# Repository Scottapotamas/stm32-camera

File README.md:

# stm32-camera

Existing products are either cameras which lack resolution and image quality (640x480 security cams that happen to have UART outputs), or are higher end expensive options geared towards computer vision for embedded hardware (openMV, PixyCam, etc).

This project seeks to provide higher quality still photos or short low-fps videos in an integrated device, allowing for greater integration flexibility whilst minimising power consumption.

# Project Goals

- Sample a CMOS camera sensor using a microcontroller. Condition the data as appropriate, and hold images in memory.
- Allow upload of image data to the host over a serial, USB, or other connection.
- Aim to minimise current draw wherever possible, and design around the ability to 'deep-sleep' for maximum power savings.
- Support a wide range of lenses for different application requirements.
- Allow the host to control functionality such as exposure, capture modes, resolution, and power saving functionality.
- Cost less than $65
- Provide source for interfacing a host device like an Arduino/STM32.
- Provide software sources for the camera board to allow modified behaviour.

# Bonus Features

- Control either an onboard or off-board LED flash. Use a DAC output to drive it for variable brightness.
- Control a IR filter switch mechanism to add or subtract IR filtering automatically at night.
- Include hardware light sensing to detect ambient light without use of the camera (for IR filter switch, dynamic flash brightness, etc).
- Ability to store images or image sequences on disk, and/or copy them off later when the action dies down.

# Approach

- Small 32x32mm PCB with camera sensor, lens mount (uses 20mm spaced M2 screws), microcontroller.
- STM32F4 microcontroller interfaces to the sensor and provides power management, filter swaps, storage etc.
- The IO pinout is 2.54mm 8-way through hole. Accepts 4-14V DC input power. Has UART, and 3 high feature set expansion IO.
- Mounting hole pattern is somewhat backwards compatible with 28mm spaced M3 holes.

# Hardware Overview

- Its a 4 layer board due to the density of the fanout and smaller board package. 
- Min track width/clearance is 0.22mm and min via is 0.35mm. No blind or buried vias.
- While a bit tight, it should be fine with better 'budget' Chinese fabs. OSHPark would have absolutely no issues with it.
- Specific notes are in [the electronics folder](Electronics)

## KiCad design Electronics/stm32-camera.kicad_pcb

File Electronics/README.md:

# Electronics Notes

General implementation notes during assignment and schematic capture. These are notes which don't make it onto the schematic due to length or relevance. Hopefully they might be useful during software dev.

# Microcontroller Pin Assignment

- I2C2 peripheral is used for SSCB interface (configuration registers).
- MCO (PA8) is used for the camera XCLK clock. Should clock at 24Mhz typical, 6Mhz minimum. This can be the HSI, HSE, a timer, etc.
- DCMI interface is used for main camera connection (includes HSYNC/VSYNC/PIXCK pins etc)
- PCLK is the camera strobe for 8-bit data on rising edge.
- PWDN is the camera power down signal (active high). Connected to PE3.
- RES is camera reset signal (active low). Connected to PE2
- SDIO interface is used in 4-bit mode for SD card. In theory, we should be able to write images to the SD card at highish speed, then allow the host to pull them off later if needed.
- SWD with SWO is enabled explicitly. Plan on using CORTEX 10-pin header.
- HSE clock included. Probably use a 16MHz CERALOCK instead of usual 8MHz?
- DAC2 is proposed for use with a flash driver. Ideally don't use PWM as switching noise is potentially visible, but that same pin can also be an analog input, PWM output or general GPIO.

# Sensor Specifics

## Power Down Options

| Hardware Control  | Software Control |
| ----------------- | ---------------- |
| PWDN is pulled high to stop the clock  | i2c commands available but doesn't stop everything (clocks) |
| Power draw is apparently 15uA.  | Registers are retained but draws 1mA.  |

Later on in the datasheet, this is conflicted by:

> For OV2640, there have big power down current, so power down mode is not supported by OV2640 for power saving.

The lower voltage LDO's have their EN line connected to the micro for more granular/forceful control.
I'll likely just use hardware control as long as it configures fast enough.

## Reset

A full hardware reset is performed when RESETB goes low.

There is also reset via the i2c interface.

## Other lines

- The datasheet states that strobe mode allows it to operate with an external flash and(/or?) LED. 
- The pinmap guide states this defaults as an input, but is the flash control output.
- A STM32 GPIO is connected instead of flash driver (at least to know if the camera wants a flash, probably redundant info by the time we see it)

# SD Card

# IR Cut Filter Switcher

As far as I can tell, its a bistable solenoid which moves the IR cut filter infront or away from the sensor.

## Theory

The [aliexpress page I got my samples from](https://www.aliexpress.com/item/HD-3MP-IR-CUT-filter-M12-lens-Metal-mount-double-filter-switcher-for-cctv-camera-IRCUT/32785570950.html?spm=2114.13010608.0.0.Kv2NdH ) has no real information other than images (but hey, $2.50AUD).

This [ebay page](http://www.ebay.com/itm/400938137287) seems to have more info (copied below)

- Working Voltage: 5V-18V
- Rated Current: 0.2A
- Screw thread interface: M12 Mount (MTV / C)
- Switcher Type: Pendulum Switcher
- Filter: Phosphate Filter
- Glass Size: 11*9.3mm
- Hole Spacing: 20mm
- Total length: 30mm. Inner Diameter: 15mm

I found another page with similar looking units which states the following:

- Start voltage: 1.8V±10%
- Applied voltage: 3.0V±10%
- Driver pulse width: 50ms
- Trigger current: 100mA or less
- Working current: 200mA or less

~~If the filter needs to be held in place during aquisition then some interesting software might need to manage the power consumption cleverly.~~ Pendulum switching means a short pulse high or low to set and forget. Drive with inverted polarity to change back.
This seems to vary between modules. Some of the other samples I received later *are* spring loaded.

It appears the units I recieved use a 1.25mm pitch molex(?) 2-pin connector. 
I'm pretty sure its molex because locking tab instead of slot. 
Seems like a Picoblade connector.

## Testing

Tests with bench supply show switching latches setting after power is removed.

With the supply set to 3.000V, the minimum current which triggers a full switch is 60mA. At 40mA and above, it appears to half-hold and reset on removal of power. Below 40mA nothing happens.

Switching would not occur at 2.0V. At 2.5V 50mA was able to activate the shutter, but 60-70mA was more reliable.

At 3.250V (rough design target for regulator and hence micro VDD) 45mA was enough to trigger a switch but sounded 'slower'. It seems the solenoid will draw 54mA, or 0.175W.

As some of these cameras will be in potentially extreme outdoor environments, a switching unit was cooled to -10°C and tested. 
At the same 3.250V, it requires 60mA to switch (0.195W). 

## Decision

It is unclear how the power requirements might change with manufacturing tolerances, temp cycling etc. Effects such as stiction etc haven't been tested for.

A 100mA spec'ed H-Bridge driver or equiv is probably the route to go.

As this eats a lot of room on the board using even small H-bridge drivers, and cost is a luxury, I'm strongly considering using multiple parallel GPIO pins (shared port for bitwise simultaneous control) to allow for push pull drive. As we only need short impulses this seems reasonable.

Unclear if the body diodes in the micro will be happy with this arrangement.

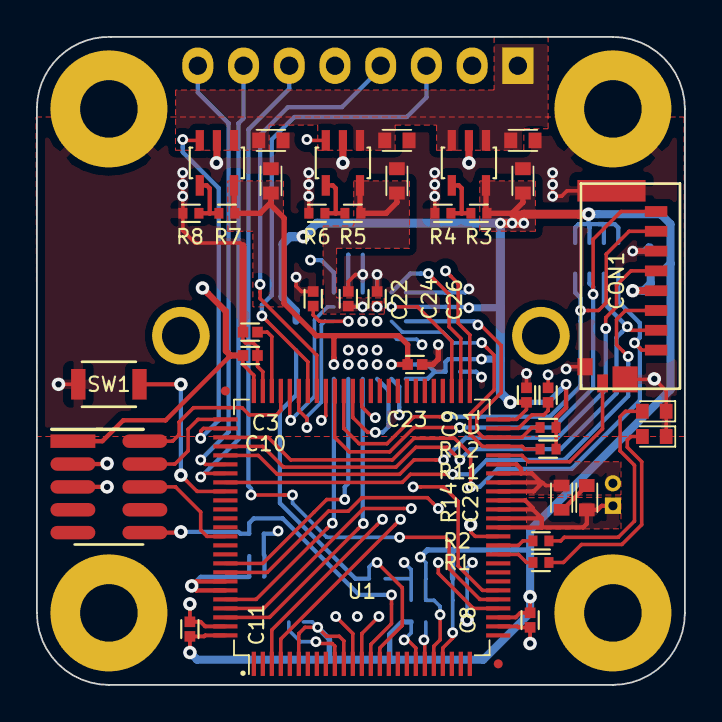
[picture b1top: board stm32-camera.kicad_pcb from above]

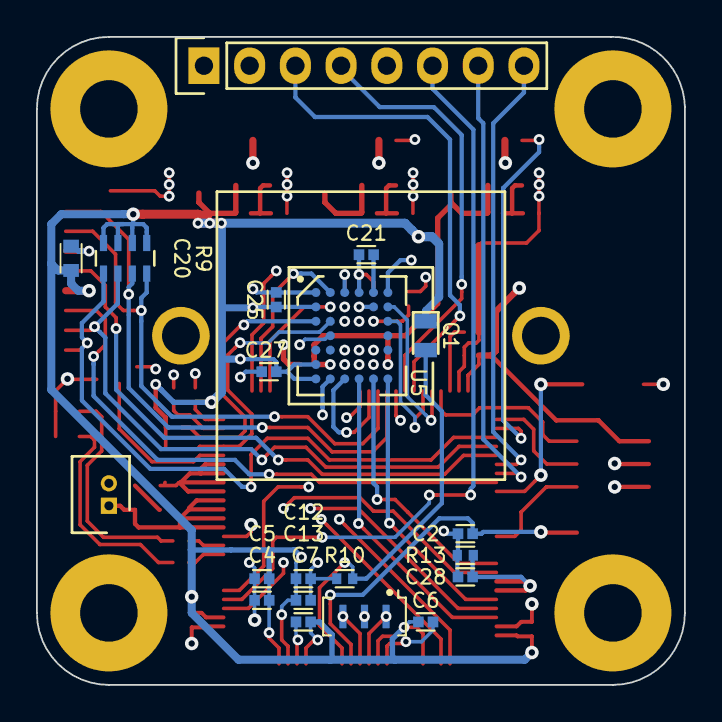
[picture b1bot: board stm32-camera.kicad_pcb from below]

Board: 4 copper layers, 36.0 x 36.0 mm, 62 parts (21 on the bottom side), 60 nets.

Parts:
C1, C3, C4, C12, C24, C28: 1UF_X5R_1005M; CAPC1005X60N
C2, C5, C6, C7, C8, C9, C10, C11, C13, C21, C22, C25, C26, C27: 100NF_X7R_1005M; CAPC1005X60N
C14, C15, C16, C17, C18, C19, C20: 2.2UF_X7R_1608M; CAPC1608X90L
C23: 4.7UF_X5R_1005M; CAPC1005X60N
C29: 100NF_X7R_1608M; CAPC1608X90L
CON1: MOLEX_47309-2651
D1: LED_GREEN_1608M; LEDC1608X80L40L
D2: LED_RED_1608M; LEDC1608X80L40L
MNT1, MNT2, MNT3, MNT4: MNT_M3_PLATED; MTGP650H330
MP1: M12_LENS_MOUNT_IR_SWITCHNG; M12x0.5_LENS_MOUNT_IR_SWITCHNG
P1: CONN_01X08; Socket_Strip_Straight_1x08
P2: MOLEX_PICO_PTH_VERT_2_WAY; MOLEX_PICOBLADE_53047-0210
Q1: TEMT7000X01; TEMT7000X
R1, R2: 1K_1005M; RESC1005X40N
R3: 51K_1005M; RESC1005X40N
R4: 82K_1005M; RESC1005X40N
R5: 47K_1005M; RESC1005X40N
R6: 56K2_1005M; RESC1005X40N
R7: 100K_1005M; RESC1005X40N
R8: 3K6_1005M; RESC1005X40N
R9: 47K_QUAD_ARRAY_1608M; R_Array_Concave_4x1608M
R10: 10K_1005M; RESC1005X40N
R11, R12: 4K7_1005M; RESC1005X40N
R13: 510K_1005M; RESC1005X40N
R14: 100R_1608M; RESC1608X50L
SW1: B3U-1000P_SPST-NO_SMD; B3U-1000P
U1: STM32F429VET6; QFP50P1600X1600X160-100L25L
U2, U3, U4: AP2210K-ADJ; SOT95P280X145-5L30N
U5: OV02640-VL9A; OV2640_CSP_38
X1: CSTCE16M0V53A; OSCSC-CSCTE-CERALOCK
X2: SWD; HARWIN_M50-3600542

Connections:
+1.3V: C19.1, C23.1, R7.1, U4.5, U5.F2, U5.F6
+2.8V: C18.1, C24.1, C26.1, R5.1, U3.5, U5.B3, U5.B4, U5.B5
+3.3V: C4.1, C5.1, C6.1, C7.1, C8.1, C9.1, C10.1, C11.1, C12.1, C13.1, C17.1, C20.1, C25.1, C27.1, CON1.4, Q1.C, R3.1, R9.1, R9.2, R9.3, R9.4, R11.1, R12.1, U1.6, U1.11, U1.19, U1.21, U1.22, U1.28, U1.50, U1.75, U1.100, U2.5, U5.B1, U5.F1, U5.G1, X2.1
+BATT: C14.1, C15.1, C16.1, P1.1, U2.1, U2.3, U3.1, U4.1
AMBIENT_LIGHT: Q1.E, R10.1, U1.15
BUTTON0: SW1.1, U1.84
D0: U1.63, U5.F3
D1: U1.64, U5.G3
D2: U1.97, U5.F4
D3: U1.98, U5.G4
D4: U1.3, U5.E5
D5: U1.92, U5.G5
D6: U1.4, U5.F5
D7: U1.96, U5.G6
EXPSTB: U1.52, U5.A2
EXP_0: P1.7, U1.82
EXP_1: P1.8, U1.81
FLASH_DAC: P1.6, U1.30
FREX: U1.53, U5.B2
GND: C1.2, C2.2, C3.2, C4.2, C5.2, C6.2, C7.2, C8.2, C9.2, C10.2, C11.2, C12.2, C13.2, C14.2, C15.2, C16.2, C17.2, C18.2, C19.2, C20.2, C21.2, C22.2, C23.2, C24.2, C25.2, C26.2, C27.2, C28.2, CON1.6, CON1.G1, CON1.G2, CON1.G4, D1.C, D2.C, MNT1.1, MNT2.1, MNT3.1, MNT4.1, P1.2, P1.5, R4.2, R6.2, R8.2, R10.2, R13.2, SW1.2, U1.10, U1.20, U1.27, U1.37, U1.74, U1.99, U2.2, U3.2, U4.2, U5.A1, U5.A3, U5.A4, U5.E4, U5.G2, X1.2, X2.3, X2.5
HREF: U1.29, U5.C3
IRCUT_A: C29.1, P2.1, U1.38, U1.39, U1.40, U1.41
IRCUT_B: P2.2, R14.2, U1.42, U1.43, U1.44, U1.45
MICROSD_CK: CON1.5, U1.80
MICROSD_CMD: CON1.3, U1.83
MICROSD_D0: CON1.7, R9.8, U1.65
MICROSD_D1: CON1.8, R9.7, U1.66
MICROSD_D2: CON1.1, R9.5, U1.78
MICROSD_D3: CON1.2, R9.6, U1.79
MICROSD_DETECT: CON1.G3, U1.46
NRST: C2.1, U1.14, X2.10
unnamed: C1.1, U1.49
unnamed: C3.1, U1.73
unnamed: C21.1, U5.A5
unnamed: C22.1, U5.C5
unnamed: C29.2, R14.1
unnamed: D1.A, R1.2
unnamed: D2.A, R2.2
unnamed: R3.2, R4.1, U2.4
unnamed: R5.2, R6.1, U3.4
unnamed: R7.2, R8.1, U4.4
unnamed: U1.12, X1.1
unnamed: U1.13, X1.3
PIXCK: U1.31, U5.E3
PWDN: U1.71, U5.B6
PWR_EN: U1.77, U3.3, U4.3
REBOOT_LATCH: C28.1, R13.1, U1.94, U1.95
RESET: U1.70, U5.C6
SIO_C: R11.2, U1.47, U5.C2
SIO_D: R12.2, U1.48, U5.C1
STATUS0: R1.1, U1.35
STATUS1: R2.1, U1.36
STROBE: U1.51, U5.A6
SWDCLK: U1.76, X2.4
SWDIO: U1.72, X2.2
SWO: U1.89, X2.6
UART_RX: P1.3, U1.69
UART_TX: P1.4, U1.68
VSYNC: U1.93, U5.D2
XCLK: U1.67, U5.C4

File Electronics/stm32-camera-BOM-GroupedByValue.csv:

"Title:",""
"Rev:","A"
"Source:","F:\Projects\stm32-camera\Electronics\stm32-camera.sch"
"Date:","25/06/2017 1:23:17 AM"
"Component Count:","53"

"Ref","Qty","Value","Description","Manf","Manf#","Installed","Footprint"
"C1, C3, C4, C12, C20, C24","6","1UF_X5R_1005M","CAP, MLCC, X5R, 1UF, 35V, 0402, 1005M","TDK","C1005X5R1V105K050BC"," ","CAPC1005X60N"
"C14, C15, C16, C17, C18, C19","6","2.2UF_X7R_1608M","CAP, MLCC, X7R, 2.2UF, 50V, 0603","MURATA","GRM188R61H225KE11D"," ","CAPC1608X90L"
"C2, C5, C6, C7, C8, C9, C10, C11, C13, C21, C22, C25, C26, C27","14","100NF_X7R_1005M","CAP, MLCC, X7R, 100NF, 50V, 0402, 1005M","TDK","CGA2B3X7R1H104K050BB"," ","CAPC1005X60N"
"C23","1","4.7UF_X5R_1608M","CAP, MLCC, X5R, 4.7UF, 16V, 0603","TDK","C1608X5R1C475K080AC"," ","CAPC1608X90L"
"CON1","1","MOLEX_47309-2651","Molex SMD Compact Micro SD Card Connector, Push-Pull Insertion, Floating Card","MOLEX","47309-2651"," ","MOLEX_47309-2651"
"D1","1","LED_GREEN_1608M","DIALIGHT ChipLED Green, 0603, 1608M","DIALIGHT","5988070107F"," ","LEDC1608X80L40N"
"D2","1","LED_RED_1608M","DIALIGHT ChipLED Red, 0603, 1608M","DIALIGHT","5988010107F"," ","LEDC1608X80L40N"
"MP1","1","M12_LENS_MOUNT_IR_SWITCHNG","M12x0.5 Lens Mount, Metal Body, M2-20mm holes, IR and Daylight Filter, Switchable","NOVOXY","UNKNOWN"," ","M12x0.5_LENS_MOUNT_IR_SWITCHNG"
"P1","1","HEADER_MALE_2MM_01X06","Board-To-Board Connector, 2 mm, 6 Contacts, Header, Male, M22 Series, Through Hole, 1 Rows","HARWIN","M22-2510605"," ","HDRV6W50P200_6X1_1200X200H400"
"P2","1","MOLEX_PICO_PTH_VERT_2_WAY","CONNECTOR, HEADER, 2POS, 1ROW, 1.25MM, PICOBLADE","MOLEX","53047-0210"," ","MOLEX_PICOBLADE_53047-0210"
"Q1","1","VEMT3700","PHOTO TRANSISTOR, Vishay, NPN, 120degrees, 2-Pin PLCC package","VISHAY","VEMT3700-GS08"," ","VISHAY_VEMT3700N"
"R1, R2","2","1K_1005M","RESISTOR, THICK FILM, 1K, 63mW, 1%, 0402, 1005M","VISHAY","CRCW04021K00FKED"," ","RESC1005X40N"
"R10","1","10K_1005M","RESISTOR, THICK FILM, 10K, 63mW, 1%, 0402, 1005M","VISHAY","CRCW040210K0FKED"," ","RESC1005X40N"
"R11, R12","2","4K7_1005M","RESISTOR, THICK FILM, 4.7K, 125mW, 1%, 0402, 1005M","VISHAY","CRCW08054K70FKTA"," ","RESC1005X40N"
"R3","1","51K_1005M","RESISTOR, THICK FILM, 51K, 63mW, 1%, 0402, 1005M","PANASONIC","ERA2AEB513X"," ","RESC1005X40N"
"R4","1","82K_1005M","RESISTOR, THICK FILM, 82K, 100mW, 1%, 0402, 1005M","PANASONIC","ERJ2GEJ823X"," ","RESC1005X40N"
"R5","1","47K_1005M","RESISTOR, THICK FILM, 47K, 63mW, 1%, 0402, 1005M","YAGEO","RC0402FR-0747KL"," ","RESC1005X40N"
"R6","1","56K2_1005M","RESISTOR, THICK FILM, 56.2K, 63mW, 1%, 0402, 1005M","PANASONIC","ERA2AEB5622X"," ","RESC1005X40N"
"R7","1","100K_1005M","RESISTOR, THICK FILM, 100K, 100mW, 1%, 0402, 1005M","PANASONIC","ERJ2RKF1003X"," ","RESC1005X40N"
"R8","1","3K6_1005M","RESISTOR, THICK FILM, 3.6K, 100mW, 1%, 0402, 1005M","PANASONIC","ERJ2GEJ362X"," ","RESC1005X40N"
"R9","1","47K_QUAD_ARRAY_1608M","RESISTOR, THICK FILM, 47K, 5%, 0603, 1608M, QUAD ARRAY","PANASONIC","EXB38V473JV"," ","R_Array_Concave_4x1608M"
"U1","1","STM32F429VET6","ST STM32F429VET6, ARM Cortex-M4, 32bit, 180 MHz, 512 KB Flash, 256 KB SRAM, 100 Pins","ST MICROELECTRONICS","STM32F429VET6"," ","QFP50P1600X1600X160-100L25N"
"U2, U3, U4","3","AP2210K-ADJ","AP2210K-ADJTRG1, Low Noise LDO Voltage Regulator, 300mA, Adjustable Voltage, 2%, 2.5 to 13.2 Vin, SOT23-5","DIODES ZETEX","AP2210K-ADJTRG1"," ","SOT95P280X145-5L30N"
"U5","1","OV02640-VL9A","OmniVision, Color, CMOS, Camera, 2.0 MP, UXGA 1/4""","OmniVision","OV02640-VL9A"," ","OV2640_CSP_38"
"X1","1","CSTCE8M00G55Z","Murata Ceramic Resonator, 8MHz Shear 33pF, 3-Pin SMT","Murata","CSTCE8M00G55Z-R0"," ","OSCSC-CSCTE-CERALOCK"
"X2","1","SWD","Cortex-M Debug Connector, SWD, JTAG (Header 1.27mm pitch 10-way 2x5)","HARWIN","M50-3600542"," ","HARWIN_M50-3600542"

"Tool:","Eeschema (2017-03-19 revision 2637835a1)-makepkg"
"Script:","F:\Projects\ECAD\KiCad\scripts\BOM\bom\BOM-GroupedByValue.py"

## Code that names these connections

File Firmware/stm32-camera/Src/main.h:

/**
  ******************************************************************************
  * File Name          : main.h
  * Description        : This file contains the common defines of the application
  ******************************************************************************
  * This notice applies to any and all portions of this file
  * that are not between comment pairs USER CODE BEGIN and
  * USER CODE END. Other portions of this file, whether 
  * inserted by the user or by software development tools
  * are owned by their respective copyright owners.
  *
  * Copyright (c) 2017 STMicroelectronics International N.V. 
  * All rights reserved.
  *
  * Redistribution and use in source and binary forms, with or without 
  * modification, are permitted, provided that the following conditions are met:
  *
  * 1. Redistribution of source code must retain the above copyright notice, 
  *    this list of conditions and the following disclaimer.
  * 2. Redistributions in binary form must reproduce the above copyright notice,
  *    this list of conditions and the following disclaimer in the documentation
  *    and/or other materials provided with the distribution.
  * 3. Neither the name of STMicroelectronics nor the names of other 
  *    contributors to this software may be used to endorse or promote products 
  *    derived from this software without specific written permission.
  * 4. This software, including modifications and/or derivative works of this 
  *    software, must execute solely and exclusively on microcontroller or
  *    microprocessor devices manufactured by or for STMicroelectronics.
  * 5. Redistribution and use of this software other than as permitted under 
  *    this license is void and will automatically terminate your rights under 
  *    this license. 
  *
  * THIS SOFTWARE IS PROVIDED BY STMICROELECTRONICS AND CONTRIBUTORS "AS IS" 
  * AND ANY EXPRESS, IMPLIED OR STATUTORY WARRANTIES, INCLUDING, BUT NOT 
  * LIMITED TO, THE IMPLIED WARRANTIES OF MERCHANTABILITY, FITNESS FOR A 
  * PARTICULAR PURPOSE AND NON-INFRINGEMENT OF THIRD PARTY INTELLECTUAL PROPERTY
  * RIGHTS ARE DISCLAIMED TO THE FULLEST EXTENT PERMITTED BY LAW. IN NO EVENT 
  * SHALL STMICROELECTRONICS OR CONTRIBUTORS BE LIABLE FOR ANY DIRECT, INDIRECT,
  * INCIDENTAL, SPECIAL, EXEMPLARY, OR CONSEQUENTIAL DAMAGES (INCLUDING, BUT NOT
  * LIMITED TO, PROCUREMENT OF SUBSTITUTE GOODS OR SERVICES; LOSS OF USE, DATA, 
  * OR PROFITS; OR BUSINESS INTERRUPTION) HOWEVER CAUSED AND ON ANY THEORY OF 
  * LIABILITY, WHETHER IN CONTRACT, STRICT LIABILITY, OR TORT (INCLUDING 
  * NEGLIGENCE OR OTHERWISE) ARISING IN ANY WAY OUT OF THE USE OF THIS SOFTWARE,
  * EVEN IF ADVISED OF THE POSSIBILITY OF SUCH DAMAGE.
  *
  ******************************************************************************
  */
/* Define to prevent recursive inclusion -------------------------------------*/
#ifndef __MAIN_H
#define __MAIN_H
  /* Includes ------------------------------------------------------------------*/

/* USER CODE BEGIN Includes */

/* USER CODE END Includes */

/* Private define ------------------------------------------------------------*/

#define AMBIENT_LIGHT_Pin GPIO_PIN_0
#define AMBIENT_LIGHT_GPIO_Port GPIOC
#define FLASH_OUTPUT_Pin GPIO_PIN_5
#define FLASH_OUTPUT_GPIO_Port GPIOA
#define STATUS0_Pin GPIO_PIN_0
#define STATUS0_GPIO_Port GPIOB
#define STATUS1_Pin GPIO_PIN_1
#define STATUS1_GPIO_Port GPIOB
#define SDIO_DETECT_Pin GPIO_PIN_15
#define SDIO_DETECT_GPIO_Port GPIOE
#define STROBE_Pin GPIO_PIN_14
#define STROBE_GPIO_Port GPIOB
#define EXPST_Pin GPIO_PIN_15
#define EXPST_GPIO_Port GPIOB
#define FREX_Pin GPIO_PIN_8
#define FREX_GPIO_Port GPIOD
#define XCLK_Pin GPIO_PIN_8
#define XCLK_GPIO_Port GPIOA
#define RES_Pin GPIO_PIN_11
#define RES_GPIO_Port GPIOA
#define PWDN_Pin GPIO_PIN_12
#define PWDN_GPIO_Port GPIOA
#define REG_EN_Pin GPIO_PIN_15
#define REG_EN_GPIO_Port GPIOA
#define EXP_1_Pin GPIO_PIN_0
#define EXP_1_GPIO_Port GPIOD
#define EXP_0_Pin GPIO_PIN_1
#define EXP_0_GPIO_Port GPIOD
#define BUTTON_0_Pin GPIO_PIN_3
#define BUTTON_0_GPIO_Port GPIOD
#define REBOOT_LATCH_Pin GPIO_PIN_8
#define REBOOT_LATCH_GPIO_Port GPIOB

/* USER CODE BEGIN Private defines */

/* USER CODE END Private defines */

void _Error_Handler(char *, int);

#define Error_Handler() _Error_Handler(__FILE__, __LINE__)

/**
  * @}
  */ 

/**
  * @}
*/ 

#endif /* __MAIN_H */
/************************ (C) COPYRIGHT STMicroelectronics *****END OF FILE****/

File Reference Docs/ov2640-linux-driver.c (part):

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#define   IMAGE_MODE_YUV422      0x00
#define   IMAGE_MODE_RAW10       0x04 /* (DVP) */
#define   IMAGE_MODE_RGB565      0x08
#define   IMAGE_MODE_HREF_VSYNC  0x02 /* HREF timing select in DVP JPEG output
				       * mode (0 for HREF is same as sensor) */
#define   IMAGE_MODE_LBYTE_FIRST 0x01 /* Byte swap enable for DVP
				       *    1: Low byte first UYVY (C2[4] =0)
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#define   COM9_AGC_GAIN_64x    0xA0 /* 101 :  64x */
#define   COM9_AGC_GAIN_128x   0xC0 /* 110 : 128x */
#define COM10       0x15 /* Common control 10 */
#define   COM10_PCLK_HREF      0x20 /* PCLK output qualified by HREF */
#define   COM10_PCLK_RISE      0x10 /* Data is updated at the rising edge of
				     * PCLK (user can latch data at the next
				     * falling edge of PCLK).
				     * 0 otherwise. */
#define   COM10_HREF_INV       0x08 /* Invert HREF polarity:
				     * HREF negative for valid data*/
#define   COM10_VSINC_INV      0x02 /* Invert VSYNC polarity */
#define HSTART      0x17 /* Horizontal Window start MSB 8 bit */
#define HEND        0x18 /* Horizontal Window end MSB 8 bit */
#define VSTART      0x19 /* Vertical Window start MSB 8 bit */
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
	struct soc_camera_subdev_desc	ssdd_dt;
	struct gpio_desc *resetb_gpio;
	struct gpio_desc *pwdn_gpio;
};

/*
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	dev_dbg(&client->dev, "%s: %s the camera\n",
			__func__, on ? "ENABLE" : "DISABLE");

	if (priv->pwdn_gpio)
		gpiod_direction_output(priv->pwdn_gpio, !on);

	return 0;
}
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		return PTR_ERR(priv->resetb_gpio);

	/* Request the power down GPIO asserted */
	priv->pwdn_gpio = devm_gpiod_get_optional(&client->dev, "pwdn",
			GPIOD_OUT_HIGH);
	if (!priv->pwdn_gpio)
		dev_dbg(&client->dev, "pwdn gpio is not assigned!\n");
	else if (IS_ERR(priv->pwdn_gpio))
		return PTR_ERR(priv->pwdn_gpio);

	/* Initialize the soc_camera_subdev_desc */
	priv->ssdd_dt.power = ov2640_hw_power;
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
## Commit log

2017-05-11 Putting thoughts into readme
2017-05-30 Dump of reference material and notes
2017-06-19 Add old change to readme with link
2017-06-19 Added M12 lens mount block SW part
2017-06-19 Renamed MCAD to mechanical folder
2017-06-19 Added KiCad project and sheets. Rough stubs
2017-06-19 Sensor pinout, net and global labels, lots of notes. Notes in readmes, creation of electronics specific notes file.
2017-06-19 Power labels, more global nets, text and formatting.
2017-06-20 Regulator stubs added
2017-06-20 Added SW model for IR swappable filter and lens mount
2017-06-20 Added draft cubemx file for F429 pinout tests
2017-06-20 Power supply feedback resistors placed.
2017-06-21 SD card pullups and removed inline resistors. Power labels on camera sheet.
2017-06-24 Added ir cut connector and a few other bits
2017-06-24 Fleshed out cubemx draft
2017-06-24 Results of testing ir switch units in notes doc
2017-06-24 Added proper STM32 part, did most of pinout. Swapped to some cheaper passives, added different microSD socket. Misc cleanup and formatting.
2017-06-24 Quick BoM added for pricing checks during dev.
2017-06-24 Continued development. Added lens mount part. Annotated parts and footprint association.
2017-06-24 Started pcb layout tests. Removed fiducials
2017-06-25 Part layout tests and changed some pin allocations.
2017-06-26 Repinned parts of micro to improve routing chances. Part placement, changed footprints etc. Added note in firmware folder to collate thoughts.
2017-06-29 Re-added changes from git index corruption issue. Unsure how much recovered.
2017-07-01 Routing concepts
2017-07-02 Update loose pcb files
2017-07-07 Update with minor routing changes from laptop
2017-07-09 Footprint changes, using 0805 phototransistor now. Using different headers. Added flash header output. Moved parts around again, silkscreen changes, cosmetics. Routing etc.
2017-07-09 Routing
2017-07-10 Continued messing around with layout
2017-07-13 Routed SD lines and repositioned parts. Re-pinned SD pullup array. Button connected to micro, etc.
2017-07-13 Routing, pours and cosmetic changes. Many general improvements to PCB.
2017-07-14 Routing changes and changed DRC width. Increased min track on board to .2mm. Fixed many DRC errors.
2017-07-16 Everything routed. Silkscreen cleanups. Fixed all DRC warnings.
2017-07-18 Added schematic pdf to electronics folder
2017-07-18 Added RC snubber to address #5.
2017-07-18 Updated CubeMX pinout, clocks and peripheral settings. Closed #7.
2017-07-18 Final silkscreen pass. Pin labels and branding are negative on soldermask. Let that gold shine through. Closes #6.
2017-07-18 Title blocks and updated notes in schematic pages.
2017-07-18 Title block text, removed unused layers in stackup.
2017-07-19 Added gerbers and drills file. Added renders and oshpark validation of correct output.
2017-07-19 Documentation maintenance.
2017-07-26 Fleshed out software docs for toolchain and programming.
2017-07-26 Updated CubeMX file to latest version.
2017-07-26 Added firmware flashing notes to software readme
2017-07-26 Added foundation of firmware. IO mapping, UART/ADC/DAC/UART abstraction mostly handled. Higher level abstractions partially fleshed out. Main task stubs need work.
2017-07-27 Suppressed/resolved filesystem handling build issues. Continued cleanup of boilerplate.
2017-07-27 Includes are relative paths instead of absolute. Modified some build parameters. Added .hex build product outputs.
2017-07-27 Streamlined cubemx adc into hal_adc
2017-07-28 Fixed red/green pin def to match hardware
2017-07-28 Fiddling with build and debugger settings. Updated some notes on debugger setup in readme
2017-07-29 Config ini should support all 3 aux defs
2017-07-29 Added camer related event defs, signals, timeout defines and counters, and camera task
2017-07-29 Reworked command interface with more functions
2017-07-29 Changes to ff configuration
2017-07-29 Introduced system_speed drivers
2017-07-29 Added ANALOG type to gpio abstraction layer. Added deinit to abstraction layer.
2017-07-29 ADC cleanup and validation. Handles photosensor and temp sensors in background.
2017-07-29 Renamed hardware appnote for 2640
2017-07-29 Task creation for aux, camera, file system
2017-07-29 Formatting gpio pin/port structure
2017-07-29 Fixed conflicting pin definition for SD Detect and RED led. Closes #9.
2017-07-29 Fix tick timer ifdef for this micro family
2017-07-29 Added missing unicode file for fatfs. Formatting improvements in file system task.
2017-07-30 Cleaned up GPIO config in hal_dac
2017-07-30 Formatting cleanup in aux/commands
2017-07-30 Fixes and cleanups
2017-07-30 Added printout of assert message over serial
2017-07-30 Fixed issue where auxillary config structure wasn't expecting 3 pins
2017-07-30 Added USART1 IRQHandler to hal_uart
2017-07-30 Removed hal_terminal and fixed terminal task
2017-07-30 General cleanup and smaller changes
2017-07-30 Separated powerup state logic from camera reg control. Created hal_camera to act as setup/teardown agent for reset lines etc.
2017-07-30 Added ov2640 driver files (empty)
2017-07-30 Camera state machine stubs added
2017-07-31 Added CPU load calculation and handling
2017-07-31 Added board sensor start/stop/read to command line
2017-07-31 Fixed temp conversions being 25C hotter than expected
2017-07-31 Refactor cpu load functions
2017-07-31 Added function to get the current clock frequency. Added terminal commands to request clock freq.
2017-07-31 Get/Set PLL and handle dynamic clock frequency changes.
2017-07-31 Enable print_f floats linker flag
2017-07-31 Cleanup and formatting
2017-07-31 Notes on power saving efforts
2017-07-31 Added software firmware update function
2017-07-31 SDIO DMA setup
2017-07-31 Added log task and required boilerplate
2017-08-01 Uart re-init after clock changes
2017-08-01 Formatting fixes to hal_system_speed
2017-08-01 Fleshed out hal_camera with IO control. Fixed incorrect gpio mode for STROBE pin.
2017-08-01 Cleanup of system clock change handling
2017-08-01 Terminal log cleanup and correct mask setting by default (all on)
2017-08-01 Systick init in system speed
2017-08-01 Pullup enabled for button. Removed spare button object from handler.
2017-08-01 Updated todo list.
2017-08-01 Started fleshing out sscb config functions. Removed hardware i2c stubs.
2017-08-01 Formatting fix.
2017-08-02 Added MCO to camera driver
2017-08-02 More appropriate function name for sscb initialisation
2017-08-02 Removed MCU/i2c field from IO abstraction.
2017-08-02 Removed MCO init from main systemclock setup function
2017-08-02 Made personalised hal_dcmi layer.
2017-08-02 GPIO cleanup after earlier changes
2017-08-02 Updated DCMI and DMA settings in cubemx to kinda match code
2017-08-02 Fixing warnings/errors from camera driver incomplete code
2017-08-02 DCMI and DMA configuration changes
2017-08-02 DCMI and camera handling work continued
2017-08-02 Updated todo list
2017-08-09 Added solenoid HAL layer for IO control. Fleshed out ir_filter driver to manage switching states. Added command to get/set filter state.
2017-08-09 Removed mx fatfs files etc
2017-08-09 Added DMA based read and write to sd io functions. Slow down SD and use hardware flow control.
2017-08-15 Vref sensing added.
2017-08-15 Removed todo list from task supervisor file
2017-08-16 Fixed malformed init of 'solenoid' drive causing hardfault when called.
2017-08-16 Add filter test toggle to command. Added delay between activating solenoid output and disabling.
2017-08-20 Added build info output to command set
2017-08-20 Rearranged the command interface
2017-08-20 Removed obsolete comments in commands.c
2017-08-20 Minor spelling fixes in utility files
2017-08-24 Since the filter works reliably now, remove the rapid toggle arg in cli
2017-08-24 Minor reshuffle of startup order and DMA priority
2017-08-24 filesystem task now uses the filesystem driver to get space and free space on fatfs volume
2017-08-25 Fixed SD not correctly identifying inserted card, which fixed filesystem mounting issues.
2017-08-25 Enable SDIO power saving between commands. Reduced SDIO clock divisor.
2017-08-25 Added system reboot command
2017-08-25 Renamed calls for config file manip to use read/write instead of browse/puts.
2017-08-25 Spelling fix
2017-08-26 Uses define for sd timeout, formatting
2017-08-26 Added mount and unmount requests to command handler. Reformatted some file system log strings.
2017-08-26 Slowed SD card speeds down a bit to prevent the occasional glitch during the 10MB copy tests.

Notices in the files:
Reference Docs/ov2640-linux-driver.c:
Copyright (C) 2010 Alberto Panizzo <maramaopercheseimorto@gmail.com>
Copyright 2005-2009 Freescale Semiconductor, Inc. All Rights Reserved.
Copyright (C) 2006, OmniVision
This program is free software; you can redistribute it and/or modify
it under the terms of the GNU General Public License version 2 as
published by the Free Software Foundation.
